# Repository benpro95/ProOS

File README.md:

## Modular Linux Configurator 

This repo contains all the custom scripts and programs that I run on my Raspberry Pi's and Proxmox server. Each folder is a module that has the setup scripts to automatically configure a stock Pi running Raspbian. The script sets up the Pi over the network and does not require attaching a keyboard and/or display. 

## Pi Projects

(aptcam) - Motion Detecting IR Security Camera (uploads videos to Google Drive)

(btpi) - Bluetooth Receiver (add bluetooth support to a vintage stereo system)

(hifi) - AirPlay and Bluetooth Receiver (optical and coaxial audio outputs)

(homepi) - Motion Detecting IR Security Camera Hub (for family home, two exernal cameras)

(ledgrid) - 8x8 Grid of RGB LED's (over 30 effects, each syncs up over Wi-Fi)

(ledwall) - 93 Pixel Ring of RGB LED's (over 30 effects, each syncs up over Wi-Fi)

(touchpi) - Touch Screen Home Automation Interface (runs custom web UI and controls LED strips)

** Photos of the projects are in each modules folder

## Overview

The folder 'rpi' contains the programs/configs that are global to all the Pi projects and gets installed first before the specific module gets installed. It sets up Raspbian to boot in read/only mode using an OverlayFS, meaning all SD card writes are written to RAM. Changes made are not saved unless the command 'rpi rw' is entered on the Pi. this reboots it in read/write mode.

The 'login' script that configures the Pi automatically switches to read/write mode before installing. The read/only boot was done because of OS corruption issues I encountered on the Pi's after unplugging them. In the read/only mode the Pi can be unplugged without having to login to issue the shutdown command. Other features that the global configuration has is that it disables all unnecessary disk writes and logs are written to RAM, a cleanup script is ran every 5 hours to make sure RAM usage stays low.

The global setup script can be found at 'rpi/config/installer.sh' it installs many APT packages used for the various projects. A custom web server is installed that allows for network settings to be changed using a browser. Making the Pi a embedded solution requiring no keyboard/display to setup. The web interface can change/connect to a Wi-Fi network, switch the Pi to wireless hotspot mode creating its own Wi-Fi network and monitor CPU/RAM usage. The Pi will automictically switch
to hotspot mode if a local Wi-Fi network cannot be found on boot.

This repo can run on any Linux server as all the tools used are standard to most installations. The 'login' script is used to manage and setup a stock Pi. The folder names for the modules are the hostnames of each Pi on my network, the setup script will automatically change the Pi's hostname to the module name and install the custom programs when using the 'init' argument. All arguments for
the login script are listed below.

** The SSH keys for the Pi's are not included in the repo, a new private key must be generated and setup on the server at the location '.ssh/rpi.rsa' and the public key included at the location '/rpi/config/authorized_keys' this will be uploaded to the Pi the first time the login script is ran. The Pi must have root login over SSH enabled with password auth turned on at first. This will allow the login script to connect over the network to the Pi. Once the setup script is complete it will disable password auth root login and only allow the RSA key based login this is done to enhance security and allow for password-less configuration of each Pi project.

## Configuration and Login Script Arguments

Login to ProOS Pi / Server\
./login "Hostname"

Sync ProOS (quick run config script) Pi / Server\
./login "Hostname" sync

Reset ProOS (full config script) Pi Only\
./login "Hostname" reset

Reset ProOS & Reinstall Packages (full config script) Pi Only\
./login "Hostname" reinstall

Clean/Restore ProOS (delete /opt/rpi and run full config script) Pi Only\
./login "Hostname" clean

Initialize ProOS (configure a base Pi or reconfigure one) Pi Only\
./login "Module" init "Hostname"

Command Reference List\
./login cmds

Clean-up Temporary Files\
./login rmtmp

## Server VMs
** located in the 'pve' folder

(automate) - Home Automation Container (runs the custom web interface and backend services)

(files) - SMB File Server Container (software ZFS RAID 3x4TB's mirrored configuration)

(plex) - Plex Media Server (access local music and videos over the internet)

(config) - Proxmox Hypervisor (configuration for my home server)

### by Ben Provenzano III

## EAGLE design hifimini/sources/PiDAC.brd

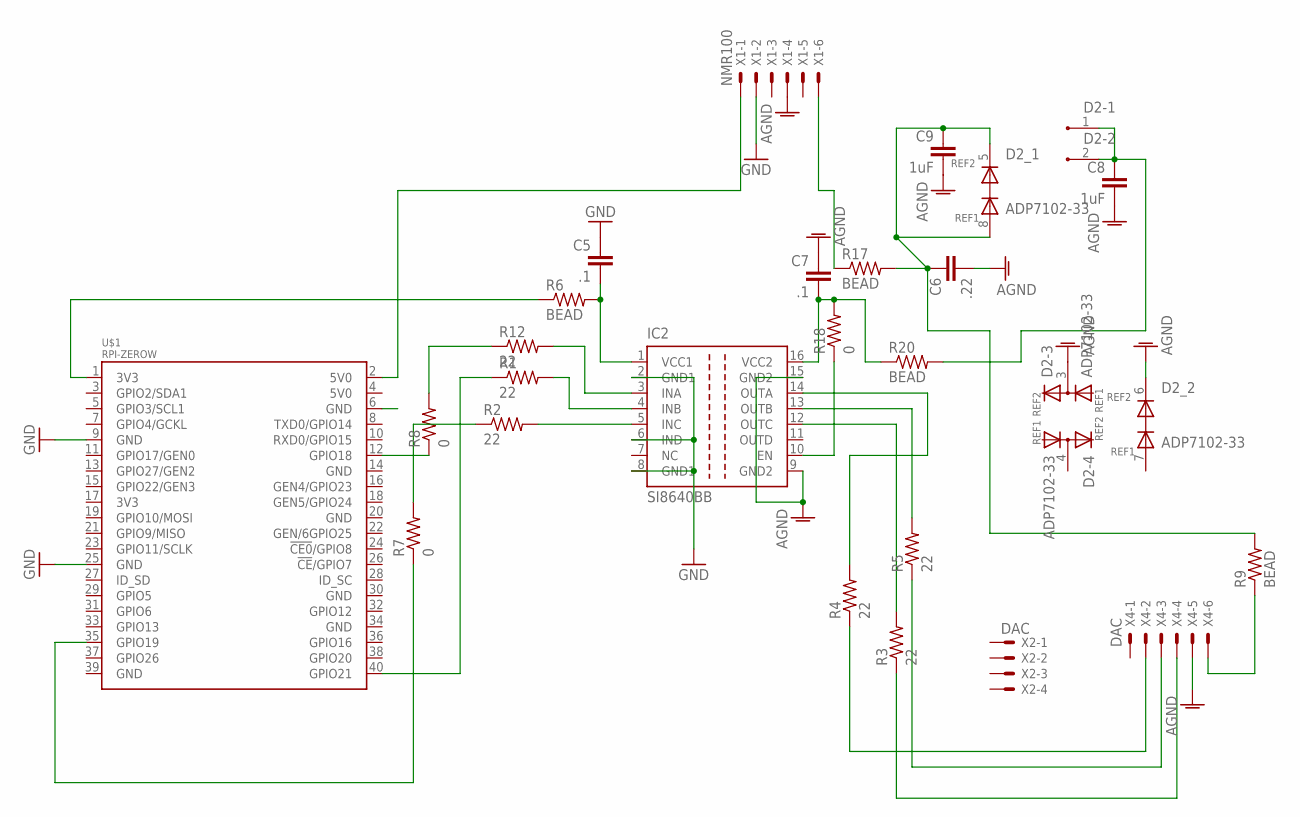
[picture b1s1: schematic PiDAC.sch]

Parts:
C5, C7: .1; C1210K
C6: .22; C1210K
C8, C9: 1uF; C1210K
D2: ADP7102-33; SO08
IC2: SI8640BB; SO-16DW
R1, R2, R3, R4, R5, R12: 22; R1210
R6, R20: BEAD; 0309/12
R7, R18: 0; 0309/10
R8: 0; 0309/12
R9, R17: BEAD; 0309/10
U$1: RPI-ZEROW; RASP_PI_ZERO_BOARD_FULL
X1: NMR100; 22-23-2061
X2: DAC; 22-23-2041
X4: DAC; 22-23-2061

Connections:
3V3@1: R6.1, U$1.1 (3V3)
5V0@1: U$1.2 (5V0), X1.1
AGND: C6.2, C7.1, C8.2, C9.2, D2.3 (K), D2.6 (REF2), IC2.9 (GND2), IC2.15 (GND2), X1.4, X4.5
GND: C5.1, IC2.2 (GND1), IC2.6 (IND), IC2.8 (GND1), U$1.9 (GND), U$1.25 (GND), X1.2
GND@8: U$1.6 (GND)
unnamed: R2.1, R7.2
unnamed: R3.1, X4.4
unnamed: R17.1, X1.6
unnamed: R5.1, X4.3
unnamed: R4.1, X4.2
unnamed: R8.1, U$1.12 (GPIO18)
unnamed: R7.1, U$1.35 (GPIO19)
unnamed: R9.1, X4.6
unnamed: C5.2, IC2.1 (VCC1), R6.2
unnamed: R8.2, R12.1
unnamed: R1.1, U$1.40 (GPIO21)
unnamed: IC2.3 (INA), R12.2
unnamed: IC2.4 (INB), R1.2
unnamed: IC2.5 (INC), R2.2
unnamed: C6.1, C9.1, D2.5 (REF2), D2.8 (REF1), R9.2, R17.2
unnamed: IC2.10 (EN), R18.1
unnamed: C8.1, D2.1 (K), D2.2 (K), R20.2
unnamed: IC2.12 (OUTC), R3.2
unnamed: IC2.13 (OUTB), R5.2
unnamed: IC2.14 (OUTA), R4.2
unnamed: C7.2, IC2.16 (VCC2), R18.2, R20.1

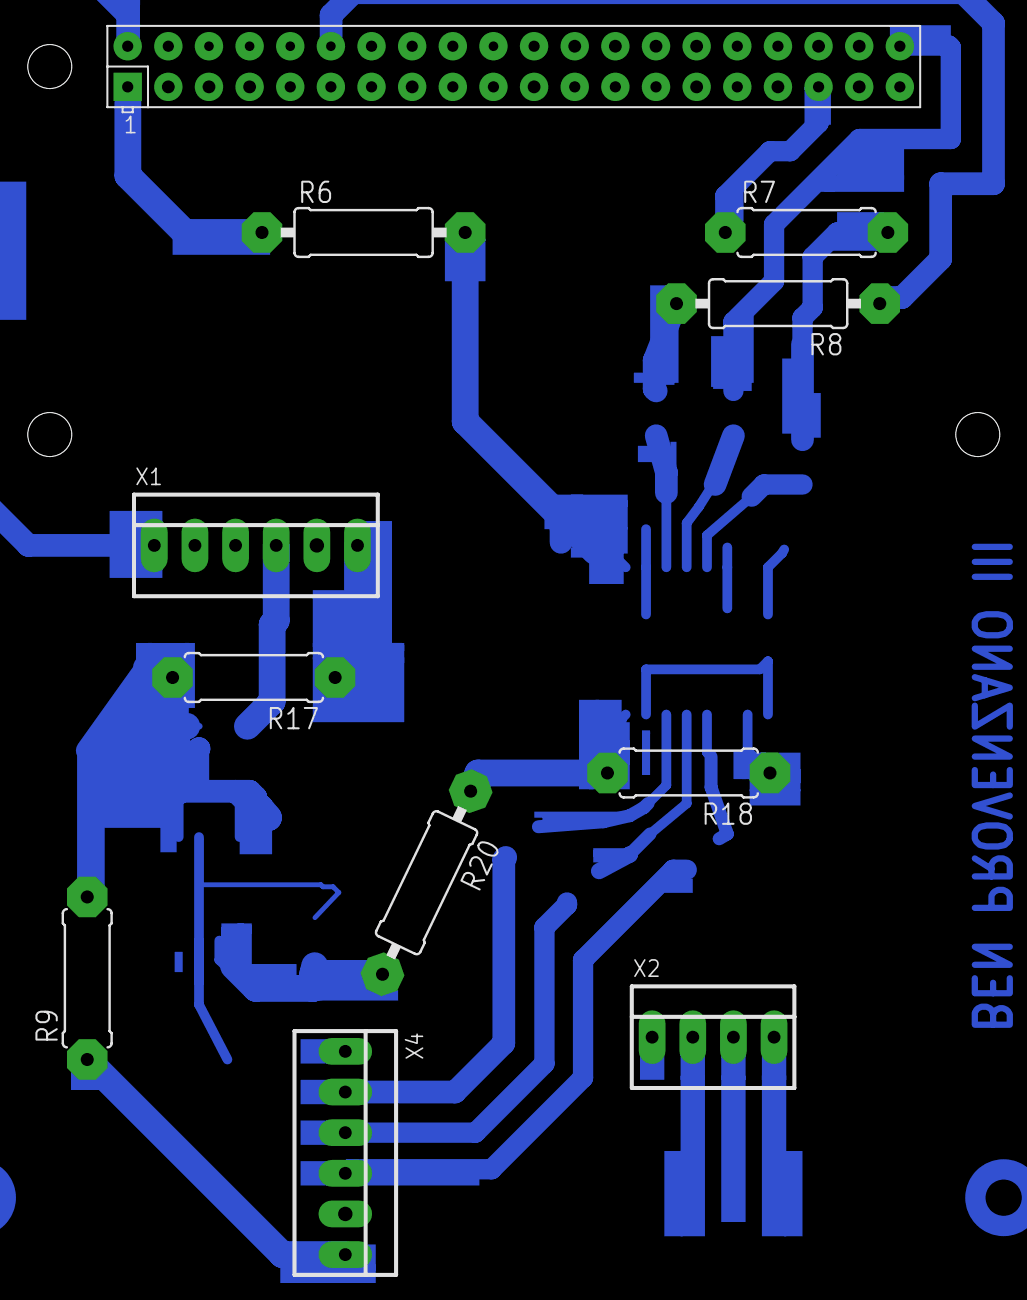
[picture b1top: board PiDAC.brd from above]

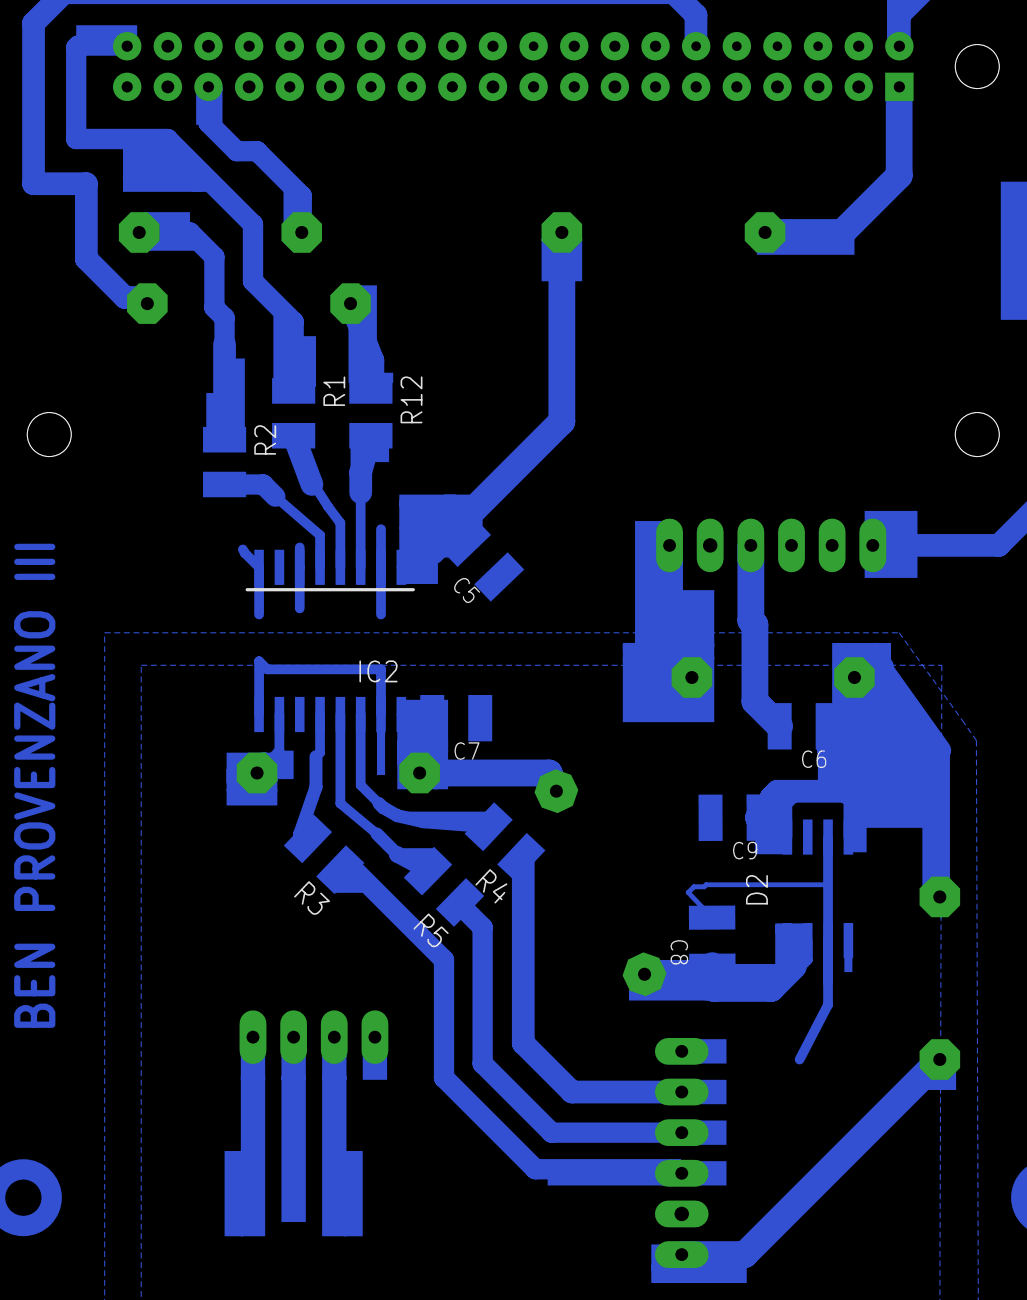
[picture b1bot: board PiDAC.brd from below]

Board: 2 copper layers, 24 parts (13 on the bottom side), 25 nets.

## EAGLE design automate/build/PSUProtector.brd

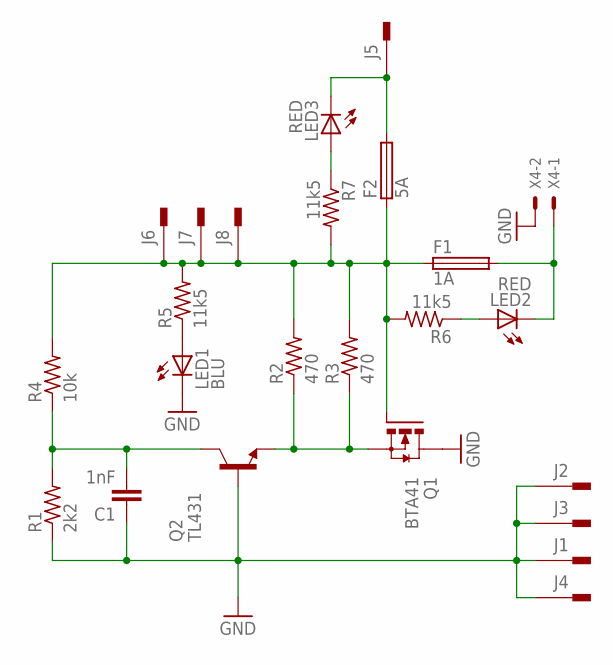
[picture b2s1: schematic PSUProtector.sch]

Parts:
C1: 1nF; C050-035X075
F1: 1A; TR5
F2: 5A; TR5
J1, J2, J3, J4, J5, J6, J7, J8: PIN2F061.040; F061.040
LED1: BLU; LED5MM
LED2, LED3: RED; LED5MM
Q1: BTA41; TO247BV
Q2: TL431; TO92-EBC
R1: 2k2; 0309/12
R2, R3: 470; 0411/15
R4: 10k; 0309/12
R5, R6, R7: 11k5; 0309/12
X4: KK-156-2

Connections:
GND: C1.1, J1.A1, J1.A2, J2.A1, J2.A2, J3.A1, J3.A2, J4.A1, J4.A2, LED1.K (C), Q1.D, Q2.B, R1.1, X4.2
unnamed: Q1.S, Q2.E, R2.1, R3.1
unnamed: F1.1, F2.1, J6.A1, J6.A2, J7.A1, J7.A2, J8.A1, J8.A2, Q1.G, R2.2, R3.2, R4.2, R5.2, R6.2, R7.2
unnamed: C1.2, Q2.C, R1.2, R4.1
unnamed: LED3.A, R7.1
unnamed: F2.2, J5.A1, J5.A2, LED3.K (C)
unnamed: LED1.A, R5.1
unnamed: F1.2, LED2.K (C), X4.1
unnamed: LED2.A, R6.1

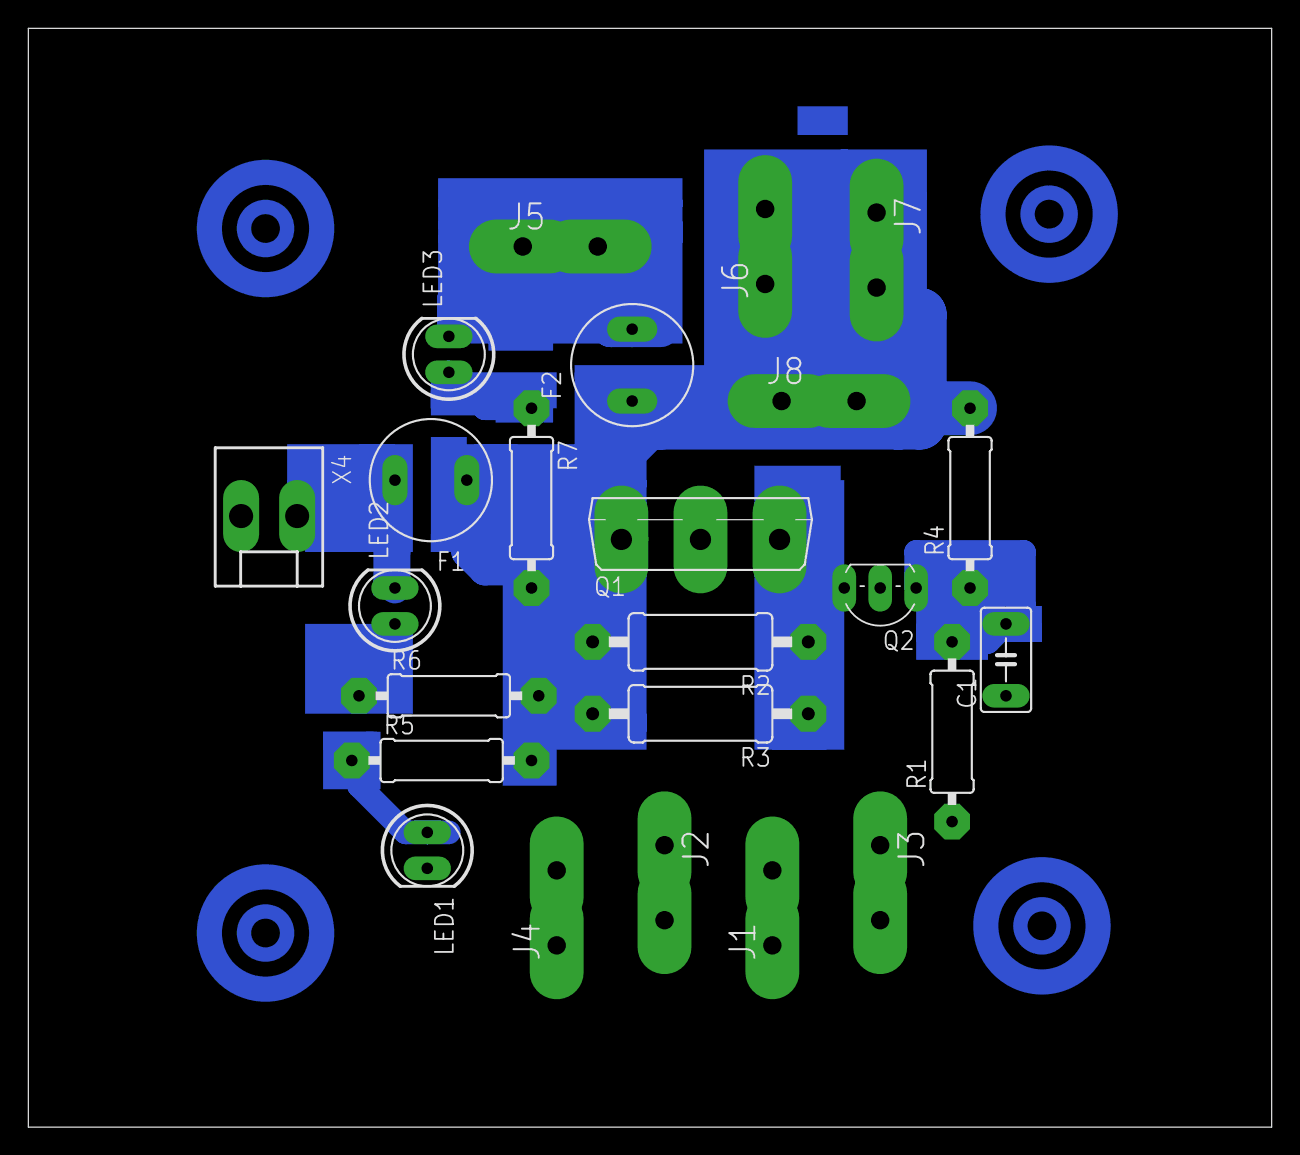
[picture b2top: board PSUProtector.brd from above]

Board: 2 copper layers, 87.9 x 77.6 mm, 24 parts (0 on the bottom side), 9 nets.

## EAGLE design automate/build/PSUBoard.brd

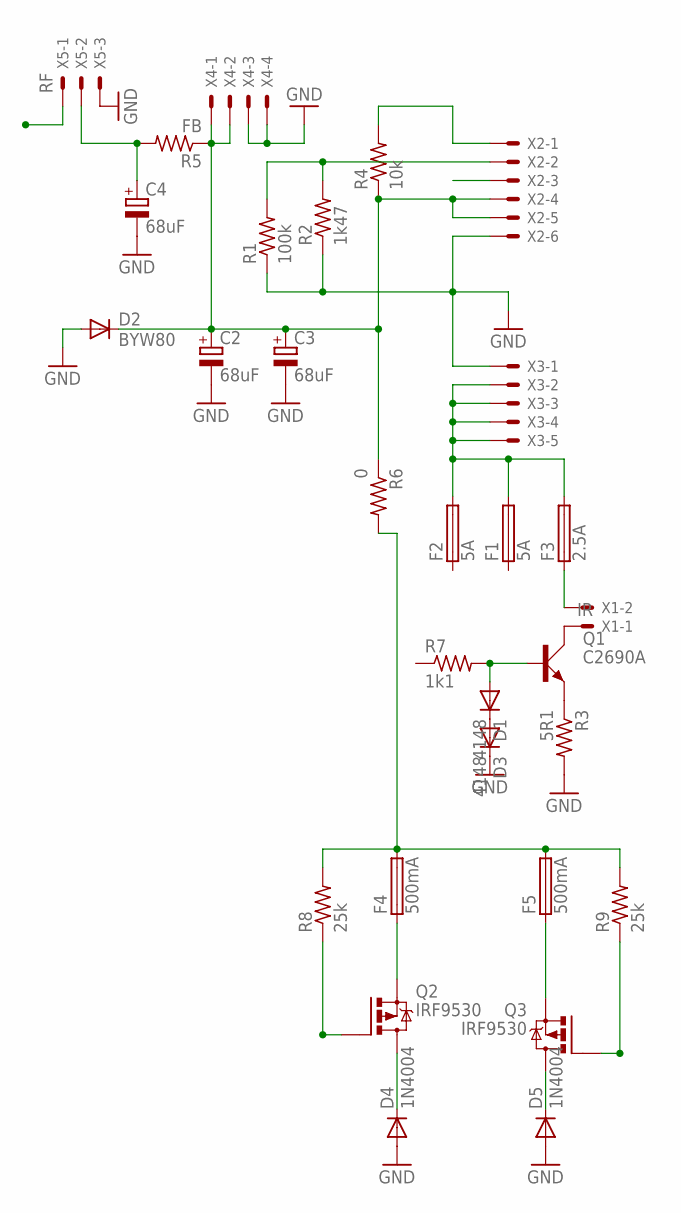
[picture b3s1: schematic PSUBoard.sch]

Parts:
C2, C3, C4: 68uF; E3,5-10
D1, D3: 4148; DO35-7
D2: BYW80; TO220ACS
D4, D5: 1N4004; DO41-10
F1, F2: 5A; TR5
F3: 2.5A; TR5
F4, F5: 500mA; TR5
Q1: C2690A; TO126AV
Q2, Q3: IRF9530; TO220BV
R1: 100k; 0309/12
R2: 1k47; 0617/22
R3: 5R1; 0309/10
R4: 10k; 0309/12
R5: FB; 0309/12
R6: 0; 0309/12
R7: 1k1; 0309/10
R8, R9: 25k; 0309/10
X1: IR; 22-23-2021
X2: 22-23-2061
X3: 22-23-2051
X4: 22-23-2041
X5: RF; 22-23-2031

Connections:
GND: C2.-, C3.-, C4.-, D2.A, D3.C, D4.A, D5.A, R1.1, R2.1, R3.2, X2.6, X3.1, X4.3, X4.4, X5.3
unnamed: C4.+, R5.2, X5.2
unnamed: F1.2, F2.2, F3.2, X3.2, X3.3, X3.4, X3.5
unnamed: C2.+, C3.+, D2.C, R4.1, R5.1, R6.1, X2.4, X2.5, X4.1, X4.2
unnamed: R4.2, X2.1
unnamed: R1.2, R2.2, X2.2
unnamed: Q1.C, X1.1
unnamed: F3.1, X1.2
unnamed: Q1.E, R3.1
unnamed: D1.C, D3.A
unnamed: D1.A, Q1.B, R7.2
unnamed: F4.2, F5.2, R6.2, R8.2, R9.2
unnamed: F4.1, Q2.S
unnamed: F5.1, Q3.S
unnamed: D4.C, Q2.D
unnamed: D5.C, Q3.D
unnamed: Q2.G, R8.1
unnamed: Q3.G, R9.1

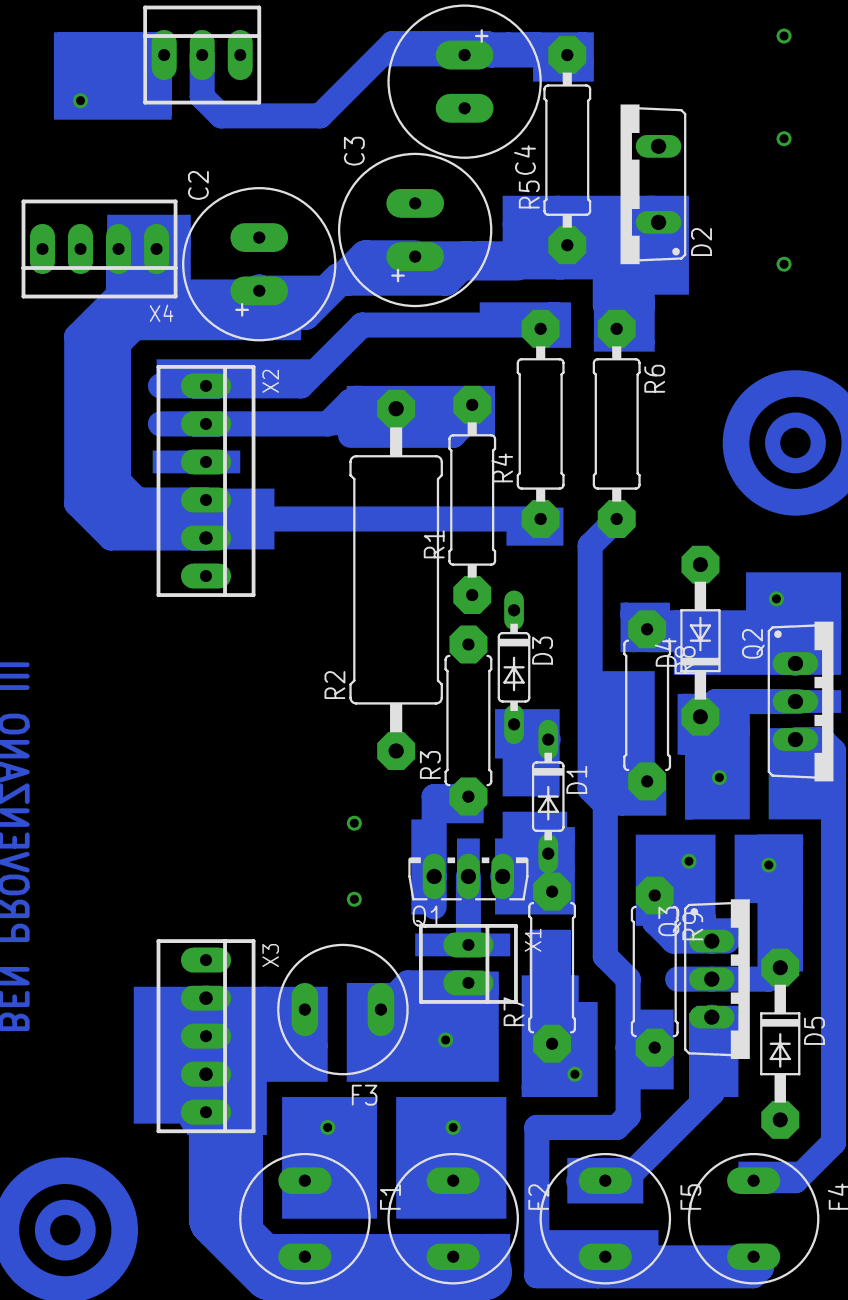
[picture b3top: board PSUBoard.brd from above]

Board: 2 copper layers, 30 parts (0 on the bottom side), 18 nets.

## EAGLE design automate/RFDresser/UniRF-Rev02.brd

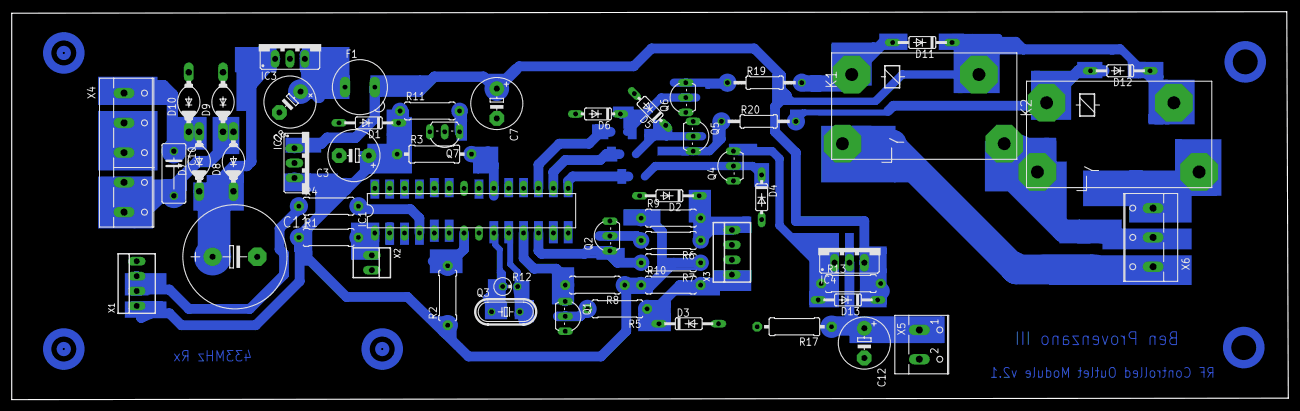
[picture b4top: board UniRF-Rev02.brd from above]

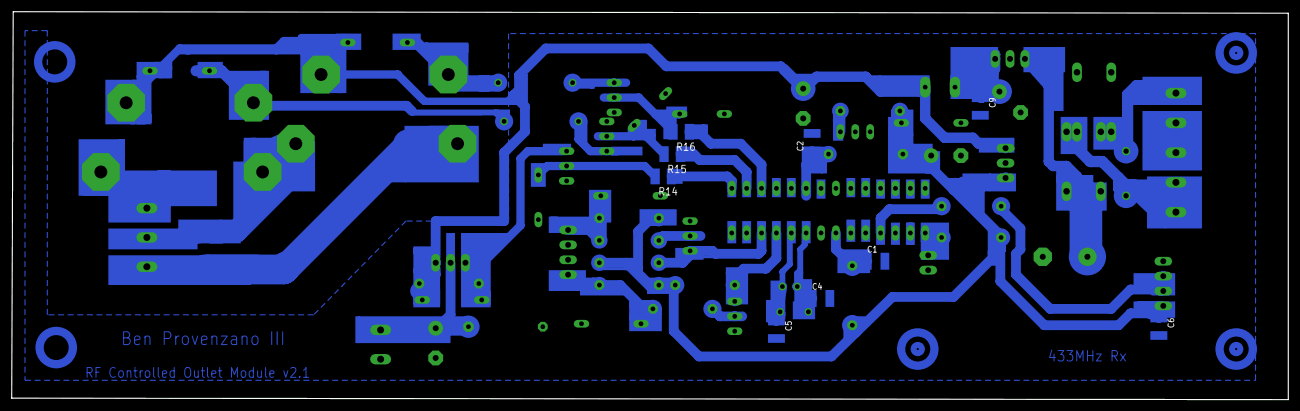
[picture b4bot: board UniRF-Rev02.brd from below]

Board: 2 copper layers, 217.9 x 66.2 mm, 64 parts (9 on the bottom side), 37 nets.

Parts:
C1, C2, C6, C9: .1; C1210K
C3, C7, C8, C12: 47uF; E5-8,5
C4, C5: 22pF; C1210K
C10: .1; C075-042X103
C11: 2200uF; E7,5-18
D1, D2, D3: TVS_5V; DO35-10
D4, D5, D6: 9V1; DO35-7
D7, D8, D9, D10: 4007; DO204-10
D11, D12: 4007; DO35-10
D13: 9V1; DO35-10
F1: 1A; 19560
IC1: ATmega328p; DIL28-3
IC2: 7805; 78XXS
IC3: 7812; 78XXS
IC4: PMOS; 78XXS
K1, K2: ALF1P12; G2RA
Q1, Q2: BC546; TO92-EBC
Q3: 16MHz; HC49/S
Q4, Q5, Q6: 2106; TO92-EBC
Q7: 3LED; TO92-EBC
R1: 10K; 0309/10
R2: BEAD; 0309/10
R3: BEAD; 0309/12
R4: 100; 0309/10
R5, R6: 330; 0309/10
R7, R8: 11K; 0309/10
R9, R10, R13: 4K7; 0309/10
R11: 2K7; 0309/10
R12: 1M; 0309V
R14, R15, R16: 1K; R1210
R17: 1K; 0309/12
R19, R20: 0; 0207/12
X1: RX_MOD; 22-23-2041
X2: RESET; 22-23-2021
X3: SWITCH; 22-23-2041
X4: W237-5P
X5: W237-102
X6: W237-103

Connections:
GND: C1.2, C2.2, C3.-, C4.2, C5.2, C6.2, C7.-, C8.-, C9.2, C11.-, C12.-, D1.A, D2.A, D3.A, D4.A, D5.A, D6.A, D9.A, D10.A, IC1.8, IC1.22, IC2.GND, IC3.GND, Q1.E, Q2.E, Q4.C, Q5.C, Q6.C, Q7.B, Q7.E, R17.2, X1.4, X2.2, X3.2, X3.3, X5.2
unnamed: D4.C, Q4.B, R14.2
unnamed: IC1.1, R1.2, X2.1
unnamed: IC1.4, R4.2
unnamed: C2.1, IC1.20, R3.2
unnamed: R4.1, X1.2, X1.3
unnamed: IC1.11, Q1.C, R8.2
unnamed: Q1.B, R5.2
unnamed: C3.+, C6.1, D1.C, IC2.OUT, R1.1, R2.1, R3.1, R7.1, R8.1, R9.1, R10.1, R11.1, X1.1
unnamed: Q2.B, R6.2
unnamed: IC1.12, Q2.C, R7.2
unnamed: C4.1, IC1.9, Q3.1, R12.1
unnamed: C5.1, IC1.10, Q3.2, R12.2
unnamed: D3.C, R5.1, R10.2, X3.1
unnamed: D2.C, R6.1, R9.2, X3.4
unnamed: D6.C, Q6.B, R16.2
unnamed: IC1.15, R14.1
unnamed: IC1.16, R15.1
unnamed: IC1.17, R16.1
unnamed: D5.C, Q5.B, R15.2
unnamed: Q7.C, R11.2
unnamed: C7.+, D11.C, D12.C, D13.C, F1.2, IC2.IN, IC4.OUT, K1.1, K2.1, R13.2
unnamed: C8.+, C9.1, F1.1, IC3.OUT
unnamed: C10.2, D8.A, D9.C, X4.4, X4.5
unnamed: D13.A, IC4.IN, Q4.E, R13.1
unnamed: Q5.E, R20.1
unnamed: Q6.E, R19.1
unnamed: C10.1, D7.A, D10.C, X4.1
unnamed: C11.+, D7.C, D8.C, IC3.IN
unnamed: C12.+, IC4.GND, R17.1, X5.1
unnamed: D11.A, K1.S, R19.2
unnamed: C1.1, IC1.7, R2.2
unnamed: K2.2, X6.3
unnamed: X4.2, X4.3
unnamed: D12.A, K2.S, R20.2
unnamed: K1.P, X6.1
unnamed: K1.2, K2.P, X6.2

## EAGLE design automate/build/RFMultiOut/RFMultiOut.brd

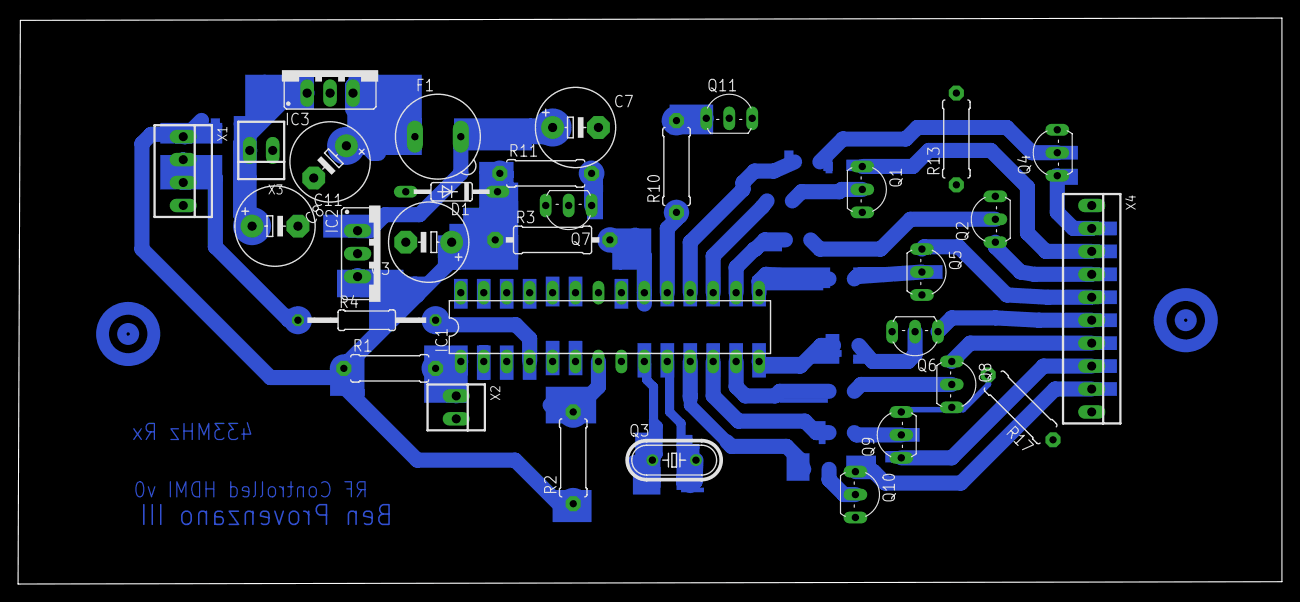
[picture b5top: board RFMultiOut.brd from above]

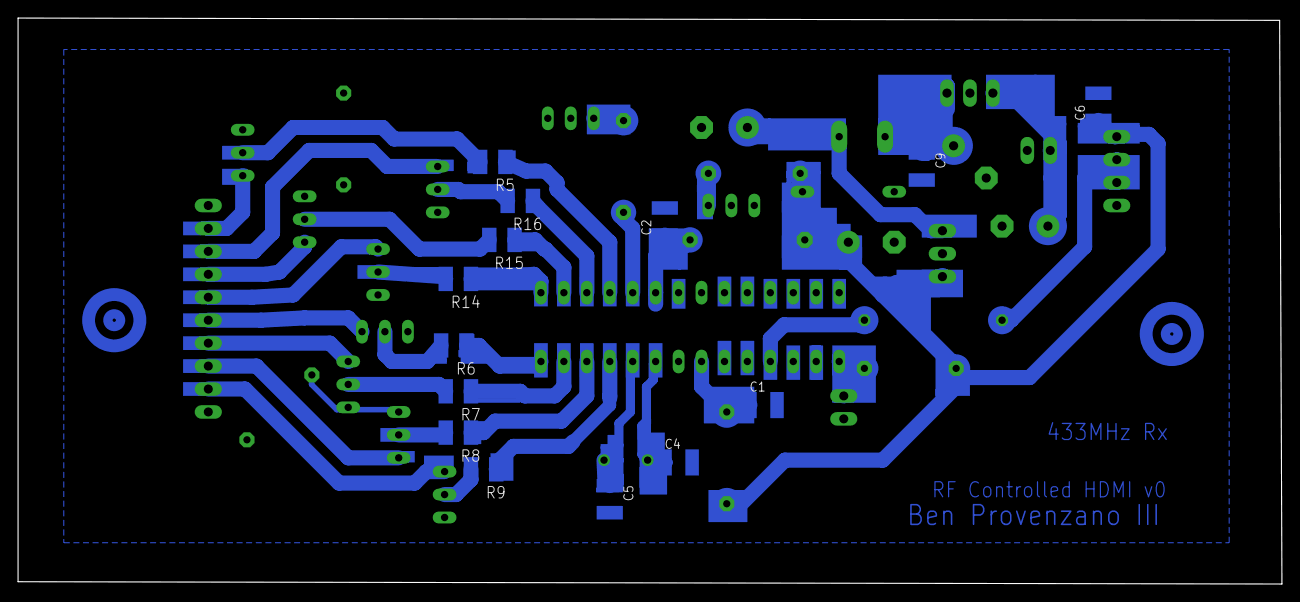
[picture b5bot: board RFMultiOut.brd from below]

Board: 2 copper layers, 139.9 x 62.7 mm, 46 parts (14 on the bottom side), 39 nets.

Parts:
C1, C2, C6, C9: .1; C1210K
C3, C7, C8: 47uF; E5-8,5
C4, C5: 22pF; C1210K
C11: 2200uF; E5-8,5
D1: TVS_5V; DO35-10
F1: 1A; 19560
IC1: ATmega328p; DIL28-3
IC2: 7805; 78XXS
IC3: 7812; 78XXS
Q1, Q2, Q4, Q5, Q6, Q8, Q9, Q10: BC546; TO92-EBC
Q3: 16MHz; HC49/S
Q7, Q11: 3LED; TO92-EBC
R1: 10K; 0309/10
R2: BEAD; 0309/10
R3: BEAD; 0309/12
R4: 100; 0207/15
R5, R6, R7, R8, R9, R14, R15, R16: 470; R1210
R10, R11: 2K7; 0309/10
R13, R17: 0; 0309/10
X1: RX_MOD; 22-23-2041
X2: RESET; 22-23-2021
X3: POWER; 22-23-2021
X4: 22-23-2101

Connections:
GND: C1.2, C2.2, C3.-, C4.2, C5.2, C6.2, C7.-, C8.-, C9.2, C11.-, D1.A, IC1.8, IC1.22, IC2.GND, IC3.GND, Q1.E, Q2.E, Q4.E, Q5.E, Q6.E, Q7.B, Q7.E, Q8.E, Q9.E, Q10.E, Q11.B, Q11.E, R13.1, R13.2, R17.1, R17.2, X1.4, X2.2, X3.1, X4.1, X4.10
unnamed: IC1.14, R6.1
unnamed: IC1.1, R1.2, X2.1
unnamed: IC1.4, R4.2
unnamed: C2.1, IC1.20, R3.2
unnamed: R4.1, X1.2, X1.3
unnamed: IC1.13, R7.1
unnamed: IC1.12, R8.1
unnamed: C3.+, C6.1, D1.C, IC2.OUT, R1.1, R2.1, R3.1, R11.1, X1.1
unnamed: IC1.11, R9.1
unnamed: IC1.18, R5.1
unnamed: Q4.B, R5.2
unnamed: C4.1, IC1.9, Q3.1
unnamed: C5.1, IC1.10, Q3.2
unnamed: C7.+, F1.2, IC2.IN
unnamed: Q1.C, X4.3
unnamed: Q10.B, R9.2
unnamed: IC1.15, R14.1
unnamed: IC1.16, R15.1
unnamed: IC1.17, R16.1
unnamed: Q9.B, R8.2
unnamed: Q7.C, R11.2
unnamed: Q8.B, R7.2
unnamed: C8.+, C9.1, F1.1, IC3.OUT
unnamed: Q6.B, R6.2
unnamed: Q5.B, R14.2
unnamed: Q2.B, R15.2
unnamed: Q1.B, R16.2
unnamed: Q4.C, X4.2
unnamed: C11.+, IC3.IN, X3.2
unnamed: Q2.C, X4.4
unnamed: Q5.C, X4.5
unnamed: Q6.C, X4.6
unnamed: C1.1, IC1.7, R2.2
unnamed: Q8.C, X4.7
unnamed: Q9.C, X4.8
unnamed: Q10.C, X4.9
unnamed: Q11.C, R10.2
unnamed: IC1.19, R10.1

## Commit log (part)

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2025-04-21 2025-04-21 08:14
2025-04-22 2025-04-22 19:21
2025-04-24 2025-04-24 18:45
2025-04-24 2025-04-24 19:02
2025-04-24 2025-04-24 19:36
2025-04-25 2025-04-24 20:50
2025-04-25 2025-04-24 22:08
2025-04-25 2025-04-25 09:38
2025-04-25 2025-04-25 14:20
2025-04-26 2025-04-26 15:17
2025-04-27 2025-04-26 22:03
2025-04-27 2025-04-27 17:44
2025-04-28 2025-04-27 20:35
2025-04-28 2025-04-28 06:13
2025-04-30 2025-04-30 17:32
2025-05-03 2025-05-03 13:58
2025-05-04 2025-05-04 09:01
2025-05-04 2025-05-04 19:12
2025-05-04 2025-05-04 19:17
2025-05-04 2025-05-04 19:28
2025-05-04 2025-05-04 19:34
2025-05-04 2025-05-04 19:40
2025-05-04 2025-05-04 19:48
2025-05-04 2025-05-04 19:49
2025-05-04 2025-05-04 19:52
2025-05-05 2025-05-04 20:07
2025-05-05 2025-05-04 20:27
2025-05-05 2025-05-04 20:45
2025-05-05 2025-05-04 21:54
2025-05-05 2025-05-04 21:56
2025-05-05 2025-05-04 21:59
2025-05-05 2025-05-04 22:02
2025-05-05 2025-05-04 22:04
2025-05-05 2025-05-04 22:13
2025-05-05 2025-05-04 22:30
2025-05-05 2025-05-05 09:19
2025-05-05 2025-05-05 09:42
2025-05-05 2025-05-05 09:43
2025-05-05 2025-05-05 09:44
2025-05-05 2025-05-05 09:52
2025-05-05 2025-05-05 12:07
2025-05-05 2025-05-05 12:56
2025-05-07 2025-05-07 07:26
2025-05-08 2025-05-07 22:02
2025-05-08 2025-05-08 09:23
2025-05-09 2025-05-09 09:33
2025-05-10 2025-05-10 08:57
2025-05-10 2025-05-10 17:09
2025-05-11 2025-05-10 21:56
2025-05-11 2025-05-11 18:35
2025-05-12 2025-05-12 18:59
2025-05-14 2025-05-13 21:40
2025-05-18 2025-05-18 18:22
2025-05-19 2025-05-18 20:48
2025-05-19 2025-05-19 09:37
2025-05-21 2025-05-20 20:56
2025-05-21 2025-05-20 21:26
2025-05-21 2025-05-20 21:30
2025-05-22 2025-05-22 19:53
2025-05-23 2025-05-22 20:05
2025-05-23 2025-05-22 21:07
2025-05-24 2025-05-24 14:00
2025-05-24 2025-05-24 18:21
2025-05-24 2025-05-24 18:24
2025-05-24 2025-05-24 18:32
2025-05-24 2025-05-24 18:39
2025-05-25 2025-05-24 20:45
2025-05-25 2025-05-24 20:58
2025-05-25 2025-05-24 21:00
2025-05-25 2025-05-24 21:14
2025-05-25 2025-05-24 22:14
2025-05-25 2025-05-24 22:55
2025-05-26 2025-05-26 18:52
2025-05-26 2025-05-26 19:23
2025-05-27 2025-05-26 20:52
2025-06-01 2025-05-31 23:49
2025-06-01 2025-05-31 23:57
2025-06-01 2025-06-01 00:26
2025-06-01 2025-06-01 10:28
2025-06-02 2025-06-02 07:59
2025-06-03 2025-06-02 20:59
2025-06-04 2025-06-03 21:10
2025-06-04 2025-06-03 21:45
2025-06-05 2025-06-05 13:07
2025-06-05 2025-06-05 13:40
2025-06-05 2025-06-05 14:03
2025-06-10 2025-06-10 15:41
2025-06-12 2025-06-12 19:07
2025-06-13 2025-06-12 20:02
2025-06-13 2025-06-13 19:57
2025-06-18 2025-06-17 21:25
2025-06-19 2025-06-19 09:08
2025-06-19 2025-06-19 13:37
2025-06-19 2025-06-19 14:00
2025-06-19 2025-06-19 15:09
2025-06-19 2025-06-19 19:30
2025-06-24 2025-06-23 22:11
2025-06-25 2025-06-25 11:12
2025-06-26 2025-06-25 21:07
2025-06-26 2025-06-26 06:44
2025-06-29 2025-06-29 16:43
2025-06-29 2025-06-29 19:04
2025-06-30 2025-06-29 20:31
2025-06-30 2025-06-29 21:14
2025-06-30 2025-06-29 21:20
2025-06-30 2025-06-30 13:09
2025-07-01 2025-06-30 21:16
2025-07-03 2025-07-02 21:12
2025-07-03 2025-07-02 21:22
2025-07-03 2025-07-03 06:38
2025-07-04 2025-07-03 21:28
2025-07-05 2025-07-05 17:04
2025-07-06 2025-07-05 23:03
2025-07-06 2025-07-06 10:53
2025-07-06 2025-07-06 12:31
2025-07-06 2025-07-06 15:21
2025-07-06 2025-07-06 19:50
2025-07-07 2025-07-06 20:30
2025-07-07 2025-07-06 21:43
2025-07-07 2025-07-06 22:06
2025-07-07 2025-07-06 22:15
2025-07-07 2025-07-06 22:19
2025-07-07 2025-07-06 22:24
2025-07-07 2025-07-07 08:06
2025-07-07 2025-07-07 10:30
2025-07-07 2025-07-07 13:40
2025-07-07 2025-07-07 13:48
2025-07-07 2025-07-07 13:58
2025-07-07 2025-07-07 18:42
2025-07-10 2025-07-09 20:02
2025-07-10 2025-07-09 20:03
2025-07-10 2025-07-09 21:40
2025-07-10 2025-07-10 19:08
2025-07-11 2025-07-10 22:21
2025-07-11 2025-07-11 08:22
2025-07-11 2025-07-11 13:32
2025-07-11 2025-07-11 15:32
2025-07-12 2025-07-12 12:05
2025-07-13 2025-07-13 14:49
2025-07-13 2025-07-13 17:35
2025-07-13 2025-07-13 18:09
2025-07-13 2025-07-13 18:20
2025-07-13 2025-07-13 18:24
2025-07-13 2025-07-13 18:51
2025-07-13 2025-07-13 18:55
2025-07-14 2025-07-13 21:42
2025-07-14 2025-07-14 12:27
2025-07-14 2025-07-14 13:48
2025-07-15 2025-07-14 20:56
2025-07-16 2025-07-16 15:58
2025-07-17 2025-07-16 21:13
2025-07-17 2025-07-16 21:20
2025-07-17 2025-07-16 21:52
2025-07-18 2025-07-18 07:56
2025-07-19 2025-07-19 09:46
2025-07-19 2025-07-19 18:41
2025-07-19 2025-07-19 19:46
2025-07-20 2025-07-20 08:31
2025-07-22 2025-07-21 21:49
2025-07-22 2025-07-21 21:53
2025-07-23 2025-07-22 20:32
2025-07-23 2025-07-22 20:35
2025-07-24 2025-07-24 06:55
2025-07-25 2025-07-25 12:32
2025-07-26 2025-07-25 22:35
2025-07-26 2025-07-26 10:30
2025-07-27 2025-07-27 08:31
2025-07-27 2025-07-27 10:23
2025-07-27 2025-07-27 10:41
2025-07-27 2025-07-27 11:21
2025-07-27 2025-07-27 12:32
2025-07-27 2025-07-27 18:54
2025-07-28 2025-07-27 20:13
2025-07-28 2025-07-27 22:05
2025-07-28 2025-07-28 06:17
2025-07-28 2025-07-28 09:01
2025-07-28 2025-07-28 09:30
2025-07-28 2025-07-28 09:45
2025-07-28 2025-07-28 18:41
2025-07-28 2025-07-28 18:42
2025-07-28 2025-07-28 19:39
2025-07-28 2025-07-28 19:41
2025-07-29 2025-07-28 20:06
2025-07-29 2025-07-28 20:23
2025-07-29 2025-07-29 19:21
2025-07-30 2025-07-29 20:54
2025-07-31 2025-07-31 05:57
2025-08-02 2025-08-01 20:30
2025-08-02 2025-08-01 21:41
2025-08-02 2025-08-01 21:50
2025-08-02 2025-08-01 22:01
2025-08-02 2025-08-02 15:50
2025-08-03 2025-08-02 20:02
2025-08-03 2025-08-02 20:22
2025-08-03 2025-08-02 20:27
2025-08-03 2025-08-03 10:32
2025-08-03 2025-08-03 17:13
2025-08-03 2025-08-03 17:18
2025-08-04 2025-08-03 20:47
2025-08-04 2025-08-04 08:16
2025-08-04 2025-08-04 16:17
2025-08-04 2025-08-04 17:15
2025-08-05 2025-08-05 19:44
2025-08-06 2025-08-06 10:35
2025-08-07 2025-08-06 20:23
2025-08-07 2025-08-06 21:05
2025-08-07 2025-08-07 06:35
2025-08-07 2025-08-07 16:59
2025-08-08 2025-08-08 13:26
2025-08-08 2025-08-08 14:00
2025-08-09 2025-08-09 19:02
2025-08-09 2025-08-09 19:27
2025-08-10 2025-08-09 21:05
2025-08-10 2025-08-09 21:49
2025-08-10 2025-08-10 15:15
2025-08-10 2025-08-10 16:49
2025-08-10 2025-08-10 18:17
2025-08-11 2025-08-10 20:38
2025-08-11 2025-08-11 08:43
2025-08-11 2025-08-11 15:08
2025-08-11 2025-08-11 15:15
2025-08-11 2025-08-11 16:08
2025-08-11 2025-08-11 19:22
2025-08-11 2025-08-11 19:36
2025-08-12 2025-08-11 21:02
2025-08-13 2025-08-12 21:07
2025-08-13 2025-08-13 18:55
2025-08-16 2025-08-16 11:19
2025-08-16 2025-08-16 18:40
2025-08-17 2025-08-16 20:00
2025-08-17 2025-08-16 21:39
2025-08-17 2025-08-17 07:55
2025-08-17 2025-08-17 17:06
2025-08-17 2025-08-17 17:48
2025-08-17 2025-08-17 18:40
2025-08-17 2025-08-17 19:48
2025-08-18 2025-08-17 20:12
2025-08-18 2025-08-18 14:44
2025-08-21 2025-08-21 17:37
2025-08-22 2025-08-21 21:05
2025-08-24 2025-08-24 08:51
2025-08-25 2025-08-24 21:18
2025-08-31 2025-08-31 12:58
2025-09-04 2025-09-03 20:43
2025-09-04 2025-09-04 10:06
2025-09-06 2025-09-05 22:36
2025-09-08 2025-09-08 12:34
2025-09-08 2025-09-08 14:44
2025-09-08 2025-09-08 19:58
2025-09-13 2025-09-13 19:29
2025-09-13 2025-09-13 19:37
2025-09-14 2025-09-13 22:15
2025-09-14 2025-09-14 13:09
2025-09-14 2025-09-14 14:42
2025-09-14 2025-09-14 19:35
2025-09-15 2025-09-15 11:39
2025-09-15 2025-09-15 13:55
2025-09-15 2025-09-15 14:39
2025-09-15 2025-09-15 19:41
2025-09-19 2025-09-19 19:05
2025-09-20 2025-09-20 10:28
2025-09-21 2025-09-21 13:38
2025-09-22 2025-09-21 20:51
2025-09-22 2025-09-22 13:11
2025-09-23 2025-09-23 17:50
2025-09-24 2025-09-24 07:49
2025-09-24 2025-09-24 13:35
2025-09-24 2025-09-24 17:39
2025-09-25 2025-09-25 16:51
2025-09-27 2025-09-27 17:41
2025-09-28 2025-09-27 20:57
2025-09-29 2025-09-28 21:06
2025-10-03 2025-10-03 07:52
2025-10-03 2025-10-03 14:25
2025-10-04 2025-10-03 20:18
2025-10-04 2025-10-03 20:31
2025-10-04 2025-10-04 15:45
2025-10-04 2025-10-04 16:11
2025-10-09 2025-10-09 13:15
2025-10-10 2025-10-10 08:37
2025-10-10 2025-10-10 10:59
2025-10-10 2025-10-10 13:16
2025-10-10 2025-10-10 15:48
2025-10-13 2025-10-13 17:49
2025-10-13 2025-10-13 19:57
2025-10-15 2025-10-14 20:53
2025-10-15 2025-10-14 21:04
2025-10-16 2025-10-16 17:10
2025-10-19 2025-10-19 18:25
2025-10-23 2025-10-23 06:20
2025-10-23 2025-10-23 18:55
2025-10-26 2025-10-26 07:52
2025-10-26 2025-10-26 07:55
2025-10-26 2025-10-26 08:00
2025-10-27 2025-10-27 19:24
2025-10-29 2025-10-29 06:20
2025-10-31 2025-10-31 19:50
2025-11-28 2025-11-28 08:30
2025-11-28 2025-11-28 14:14
2025-11-28 2025-11-28 15:36
2025-11-28 2025-11-28 16:09
2025-11-29 2025-11-29 13:41
2025-11-29 2025-11-29 14:25
2025-11-29 2025-11-29 16:00
2025-12-01 2025-12-01 12:57
2025-12-03 2025-12-03 17:04
2025-12-03 2025-12-03 17:22
2025-12-03 2025-12-03 17:26
2025-12-04 2025-12-04 06:29
2025-12-05 2025-12-04 20:32
2025-12-05 2025-12-04 21:23
2025-12-05 2025-12-04 21:31
2025-12-05 2025-12-04 21:50
2025-12-05 2025-12-05 08:38
2025-12-06 2025-12-06 08:02
2025-12-07 2025-12-07 14:11
2025-12-07 2025-12-07 16:20
2025-12-08 2025-12-08 06:17
2025-12-08 2025-12-08 12:13
2025-12-08 2025-12-08 17:31
2025-12-09 2025-12-09 15:24
2025-12-11 2025-12-11 17:41
2025-12-12 2025-12-12 08:37
2025-12-14 2025-12-14 14:19
2025-12-15 2025-12-15 10:12
2025-12-18 2025-12-18 12:06
2025-12-21 2025-12-20 21:37
2025-12-21 2025-12-20 21:41
2025-12-21 2025-12-21 12:02
2025-12-21 2025-12-21 12:32
2025-12-22 2025-12-22 09:16
2025-12-22 2025-12-22 13:29
2025-12-24 2025-12-24 15:00
2025-12-24 2025-12-24 15:48
2025-12-25 2025-12-24 22:34
2025-12-27 2025-12-27 17:52
2025-12-28 2025-12-28 18:14
2025-12-29 2025-12-28 19:04
2025-12-29 2025-12-29 11:51
2025-12-30 2025-12-30 07:07
2025-12-30 2025-12-30 10:39
2025-12-30 2025-12-30 12:28
2025-12-31 2025-12-31 12:39
2025-12-31 2025-12-31 14:26
2026-01-01 2026-01-01 17:05
2026-01-01 2026-01-01 18:37
2026-01-01 2026-01-01 18:48
2026-01-01 2026-01-01 18:54
2026-01-01 2026-01-01 18:58
2026-01-02 2026-01-01 19:01
2026-01-02 2026-01-02 11:44
2026-01-04 2026-01-04 15:51
2026-01-04 2026-01-04 16:11
2026-01-04 2026-01-04 16:19
2026-01-04 2026-01-04 16:24
2026-01-05 2026-01-05 16:41
2026-01-09 2026-01-08 21:08
2026-01-09 2026-01-09 06:40
2026-01-09 2026-01-09 10:31
2026-01-09 2026-01-09 11:19
2026-01-09 2026-01-09 11:26
2026-01-09 2026-01-09 17:17
2026-01-09 2026-01-09 17:28
2026-01-10 2026-01-10 16:14
2026-01-10 2026-01-10 17:02
2026-01-13 2026-01-12 20:07
2026-01-16 2026-01-15 21:44
2026-01-17 2026-01-16 20:21
2026-01-18 2026-01-17 20:49
2026-01-18 2026-01-17 21:36
2026-01-18 2026-01-17 21:50
2026-01-18 2026-01-17 21:56
2026-01-18 2026-01-17 22:12
2026-01-18 2026-01-18 09:28
2026-01-19 2026-01-18 19:44
2026-01-19 2026-01-19 08:15
2026-01-19 2026-01-19 13:10
2026-01-19 2026-01-19 13:15
2026-01-19 2026-01-19 13:41
2026-01-19 2026-01-19 13:49
2026-01-19 2026-01-19 13:53
2026-01-20 2026-01-19 21:22
2026-01-21 2026-01-20 21:18
2026-01-21 2026-01-21 18:16
2026-01-21 2026-01-21 18:17
2026-01-22 2026-01-21 20:25
2026-01-23 2026-01-22 19:09
2026-01-23 2026-01-23 18:56
2026-01-24 2026-01-23 21:01
2026-01-25 2026-01-25 17:57
2026-01-26 2026-01-25 21:56
2026-01-26 2026-01-26 17:26
2026-01-26 2026-01-26 18:07
2026-01-27 2026-01-26 19:54
2026-01-28 2026-01-28 08:10
2026-01-28 2026-01-28 16:07
2026-01-29 2026-01-28 19:10
2026-01-29 2026-01-28 19:26
2026-01-29 2026-01-28 20:29
